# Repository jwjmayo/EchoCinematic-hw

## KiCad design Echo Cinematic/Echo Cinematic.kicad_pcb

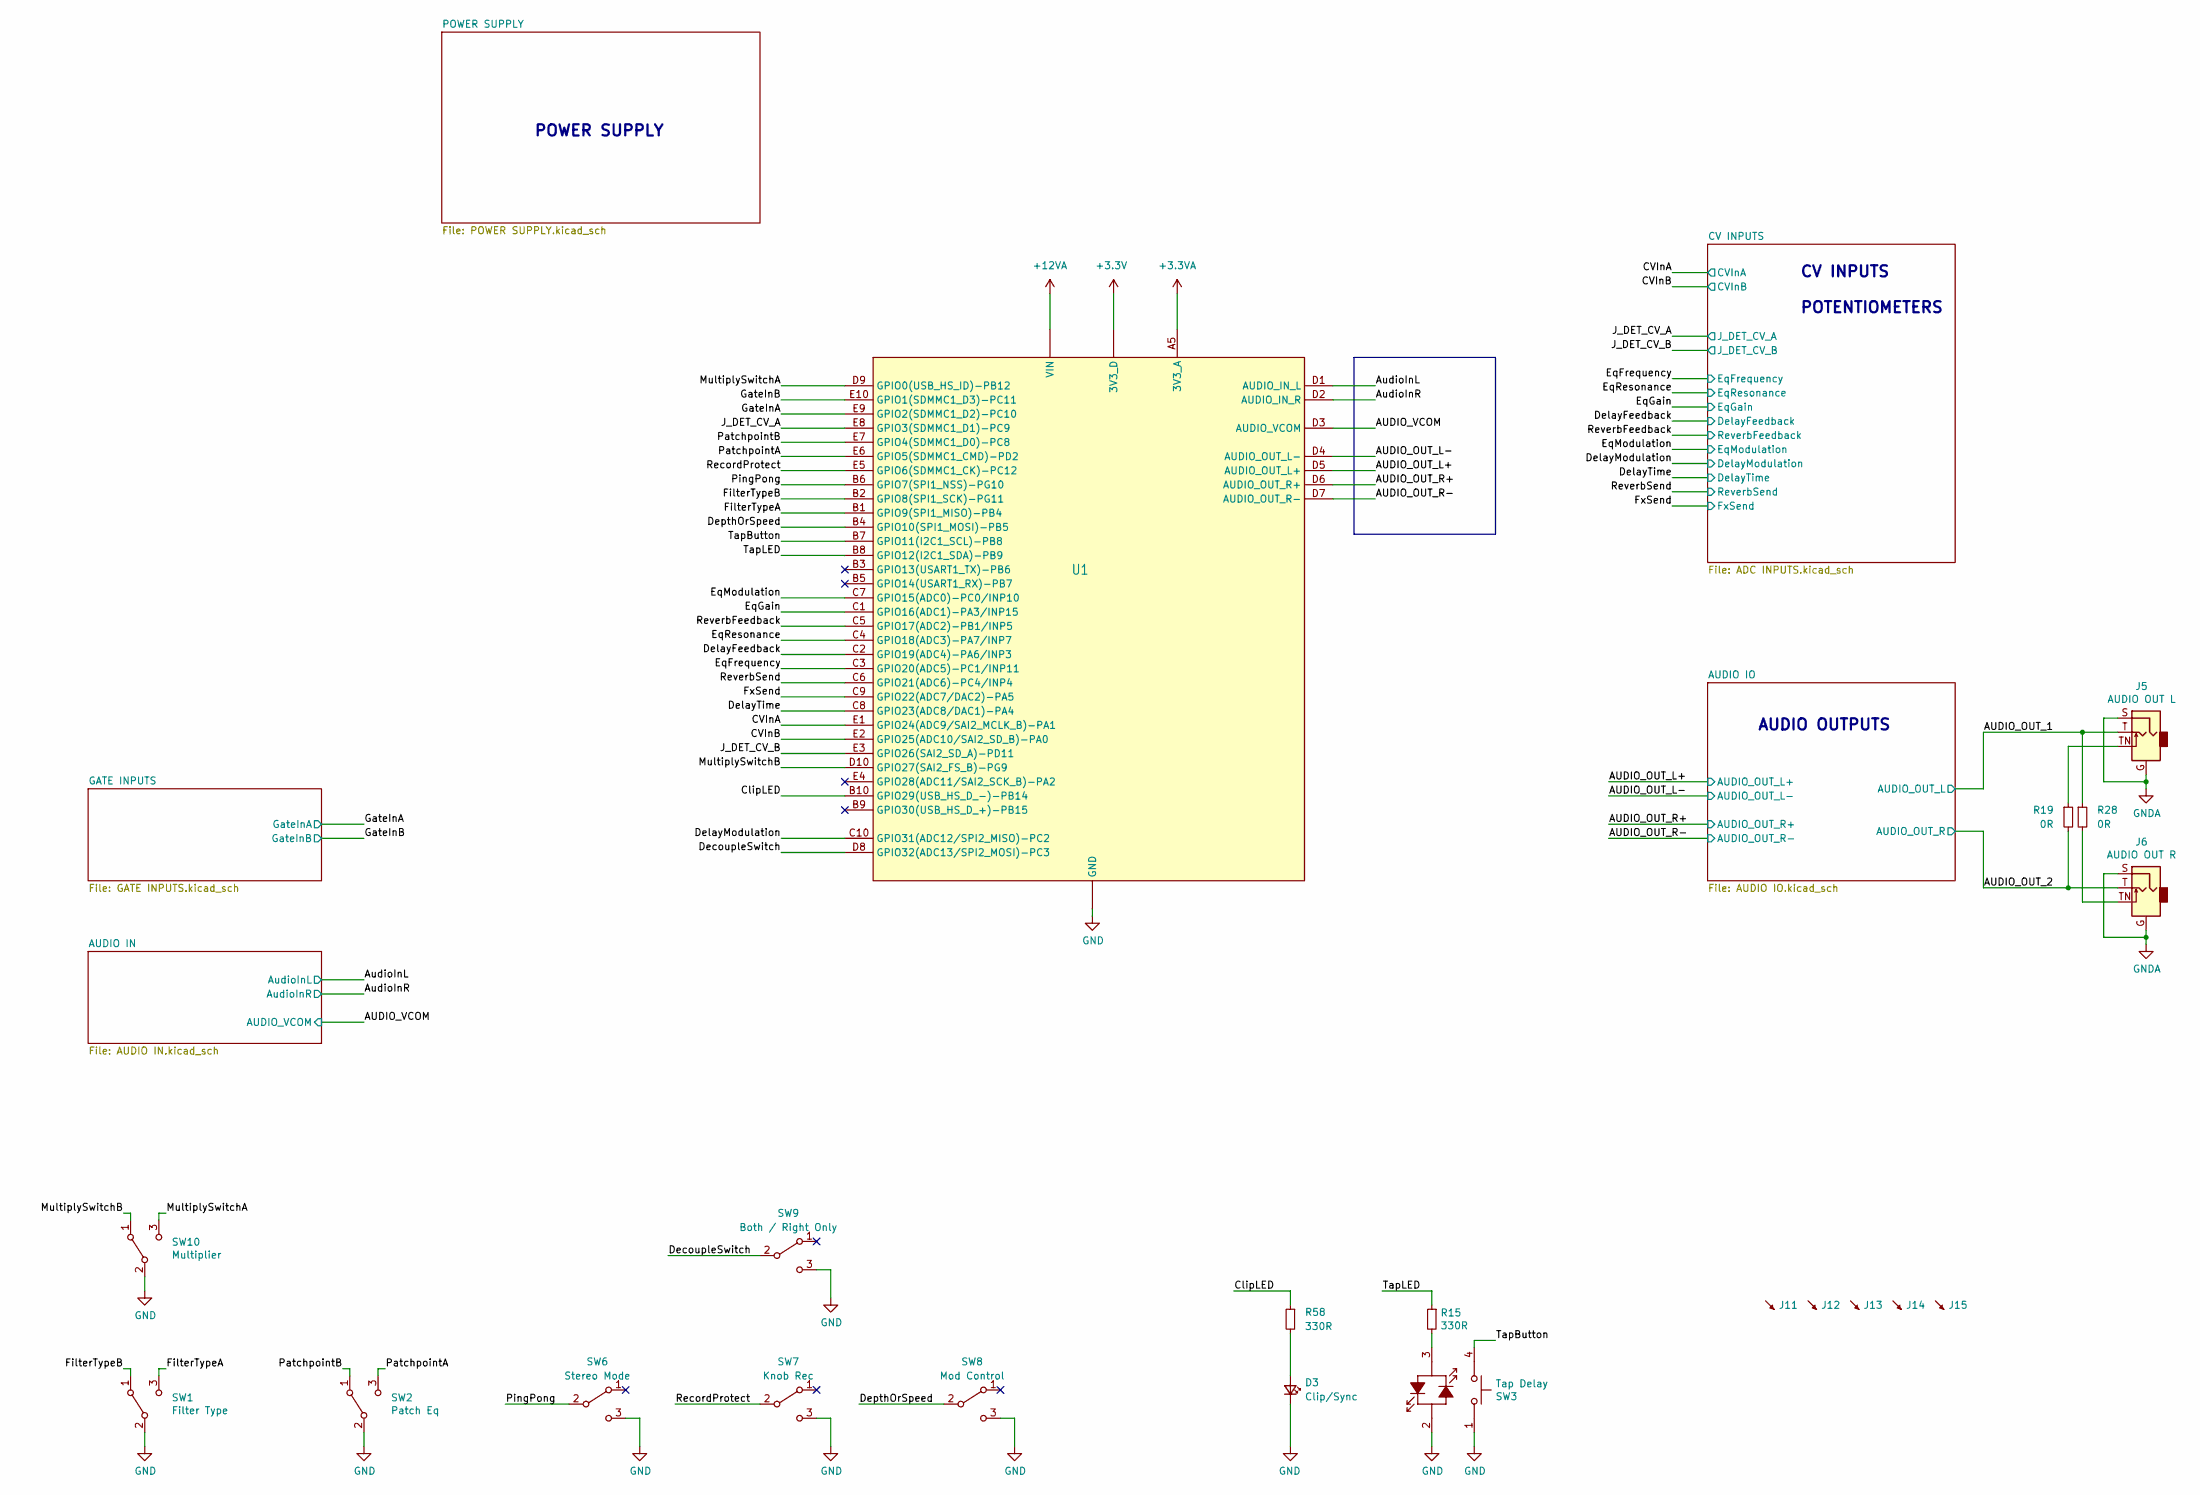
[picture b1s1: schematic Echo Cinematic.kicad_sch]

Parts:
D3: Clip/Sync; LED_D3.0mm
J5: AUDIO OUT L; THONKICONN
J6: AUDIO OUT R; THONKICONN
J11, J12, J13, J14, J15: SYM_Arrow45_Tiny; REF
R15, R58: 330R; R_0603_1608Metric
R19, R28: 0R; R_0603_1608Metric
SW1: Filter Type; SW_DWB1
SW2: Patch Eq; SW_DWB1
SW3: Tap Delay; D6R00F_LED
SW6: Stereo Mode; SW_Slide_1P2T_CK_OS102011MS2Q
SW7: Knob Rec; SW_Slide_1P2T_CK_OS102011MS2Q
SW8: Mod Control; SW_Slide_1P2T_CK_OS102011MS2Q
SW9: Both / Right Only; SW_Slide_1P2T_CK_OS102011MS2Q
SW10: Multiplier; SW_DWB1
U1: ES_DAISY_SEED2_DFM; DAISY_SEED2

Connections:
+3.3V: U1.A3 (3V3_D), U1.A4 (3V3_D); also elsewhere on the board
+3.3VA: U1.A5 (3V3_A); also elsewhere on the board
+12VA: U1.A1 (VIN), U1.A2 (VIN); also elsewhere on the board
/AUDIO_OUT_1: J5.T, R28.1; also elsewhere on the board
/AUDIO_OUT_2: J6.T, R19.2; also elsewhere on the board
/AUDIO_OUT_L+: U1.D5 (AUDIO_OUT_L+); also elsewhere on the board
/AUDIO_OUT_L-: U1.D4 (AUDIO_OUT_L-); also elsewhere on the board
/AUDIO_OUT_R+: U1.D6 (AUDIO_OUT_R+); also elsewhere on the board
/AUDIO_OUT_R-: U1.D7 (AUDIO_OUT_R-); also elsewhere on the board
/AUDIO_VCOM: U1.D3 (AUDIO_VCOM); also elsewhere on the board
/AudioInL: U1.D1 (AUDIO_IN_L); also elsewhere on the board
/AudioInR: U1.D2 (AUDIO_IN_R); also elsewhere on the board
/CVInA: U1.E1 (GPIO24(ADC9/SAI2_MCLK_B)-PA1); also elsewhere on the board
/CVInB: U1.E2 (GPIO25(ADC10/SAI2_SD_B)-PA0); also elsewhere on the board
/ClipLED: R58.1, U1.B10 (GPIO29(USB_HS_D_-)-PB14)
/DecoupleSwitch: SW9.2 (B), U1.D8 (GPIO32(ADC13/SPI2_MOSI)-PC3)
/DelayFeedback: U1.C2 (GPIO19(ADC4)-PA6/INP3); also elsewhere on the board
/DelayModulation: U1.C10 (GPIO31(ADC12/SPI2_MISO)-PC2); also elsewhere on the board
/DelayTime: U1.C8 (GPIO23(ADC8/DAC1)-PA4); also elsewhere on the board
/DepthOrSpeed: SW8.2 (B), U1.B4 (GPIO10(SPI1_MOSI)-PB5)
/EqFrequency: U1.C3 (GPIO20(ADC5)-PC1/INP11); also elsewhere on the board
/EqGain: U1.C1 (GPIO16(ADC1)-PA3/INP15); also elsewhere on the board
/EqModulation: U1.C7 (GPIO15(ADC0)-PC0/INP10); also elsewhere on the board
/EqResonance: U1.C4 (GPIO18(ADC3)-PA7/INP7); also elsewhere on the board
/FilterTypeA: SW1.3 (C), U1.B1 (GPIO9(SPI1_MISO)-PB4)
/FilterTypeB: SW1.1 (A), U1.B2 (GPIO8(SPI1_SCK)-PG11)
/FxSend: U1.C9 (GPIO22(ADC7/DAC2)-PA5); also elsewhere on the board
/GateInA: U1.E9 (GPIO2(SDMMC1_D2)-PC10); also elsewhere on the board
/GateInB: U1.E10 (GPIO1(SDMMC1_D3)-PC11); also elsewhere on the board
/J_DET_CV_A: U1.E8 (GPIO3(SDMMC1_D1)-PC9); also elsewhere on the board
/J_DET_CV_B: U1.E3 (GPIO26(SAI2_SD_A)-PD11); also elsewhere on the board
/MultiplySwitchA: SW10.3 (C), U1.D9 (GPIO0(USB_HS_ID)-PB12)
/MultiplySwitchB: SW10.1 (A), U1.D10 (GPIO27(SAI2_FS_B)-PG9)
/PatchpointA: SW2.3 (C), U1.E6 (GPIO5(SDMMC1_CMD)-PD2)
/PatchpointB: SW2.1 (A), U1.E7 (GPIO4(SDMMC1_D0)-PC8)
/PingPong: SW6.2 (B), U1.B6 (GPIO7(SPI1_NSS)-PG10)
/RecordProtect: SW7.2 (B), U1.E5 (GPIO6(SDMMC1_CK)-PC12)
/ReverbFeedback: U1.C5 (GPIO17(ADC2)-PB1/INP5); also elsewhere on the board
/ReverbSend: U1.C6 (GPIO21(ADC6)-PC4/INP4); also elsewhere on the board
/TapButton: SW3.4 (A), U1.B7 (GPIO11(I2C1_SCL)-PB8)
/TapLED: R15.1, U1.B8 (GPIO12(I2C1_SDA)-PB9)
GND: D3.1 (K), SW1.2 (B), SW2.2 (B), SW3.1, SW3.2, SW6.3 (C), SW7.3 (C), SW8.3 (C), SW9.3 (C), SW10.2 (B), U1.A6 (GND), U1.A7 (GND), U1.A8 (GND), U1.A9 (GND), U1.A10 (GND); also elsewhere on the board
GNDA: J5.G, J5.S, J6.G, J6.S; also elsewhere on the board
unnamed: D3.2 (A), R58.2
unnamed: J5.TN, R19.1
unnamed: J6.TN, R28.2
unnamed: R15.2, SW3.3 (K)

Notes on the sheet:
POWER SUPPLY
CV INPUTS POTENTIOMETERS
AUDIO OUTPUTS

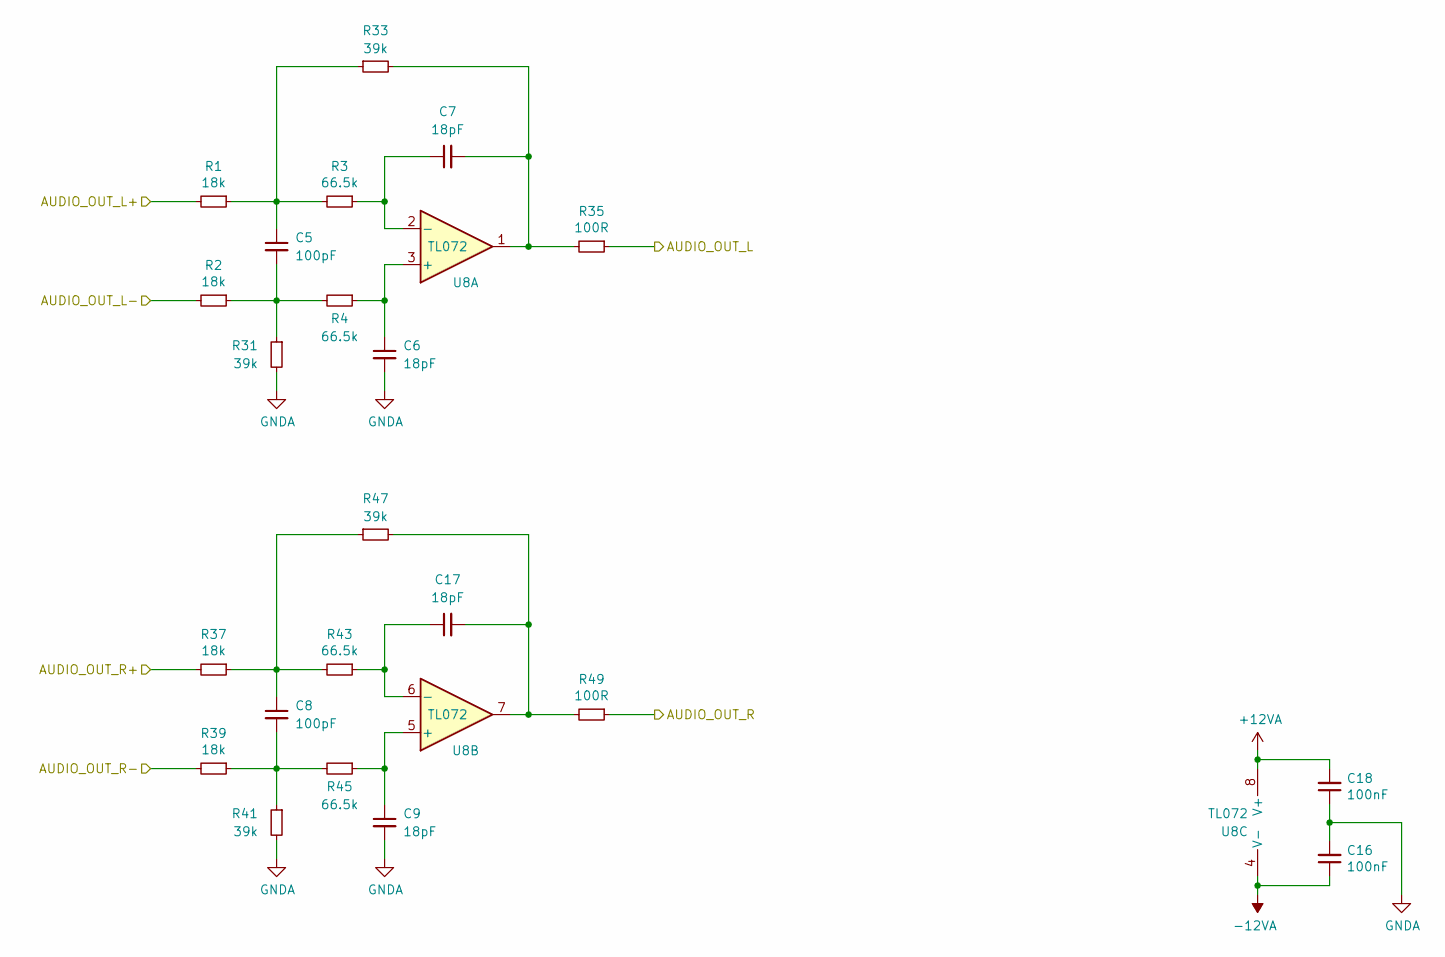
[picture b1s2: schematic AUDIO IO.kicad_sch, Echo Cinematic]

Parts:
C5, C8: 100pF; C_0603_1608Metric
C6, C7, C9, C17: 18pF; C_0603_1608Metric
C16, C18: 100nF; C_0603_1608Metric
R1, R2, R37, R39: 18k; R_0603_1608Metric
R3, R4, R43, R45: 66.5k; R_0603_1608Metric
R31, R33, R41, R47: 39k; R_0603_1608Metric
R35, R49: 100R; R_0603_1608Metric
U8: TL072; SO-8_3.9x4.9mm_P1.27mm

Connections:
+12VA: C18.2, U8.8 (V+); also elsewhere on the board
-12VA: C16.1, U8.4 (V-); also elsewhere on the board
/AUDIO_OUT_1: R35.1; also elsewhere on the board
/AUDIO_OUT_2: R49.1; also elsewhere on the board
/AUDIO_OUT_L+: R1.2; also elsewhere on the board
/AUDIO_OUT_L-: R2.2; also elsewhere on the board
/AUDIO_OUT_R+: R37.2; also elsewhere on the board
/AUDIO_OUT_R-: R39.2; also elsewhere on the board
GNDA: C6.2, C9.2, C16.2, C18.1, R31.2, R41.2; also elsewhere on the board
unnamed: C5.1, R1.1, R3.2, R33.1
unnamed: C5.2, R2.1, R4.2, R31.1
unnamed: C7.2, R33.2, R35.2, U8.1
unnamed: C8.1, R37.1, R43.2, R47.1
unnamed: C8.2, R39.1, R41.1, R45.2
unnamed: C17.2, R47.2, R49.2, U8.7
unnamed: C6.1, R4.1, U8.3 (+)
unnamed: C7.1, R3.1, U8.2 (-)
unnamed: C9.1, R45.1, U8.5 (+)
unnamed: C17.1, R43.1, U8.6 (-)

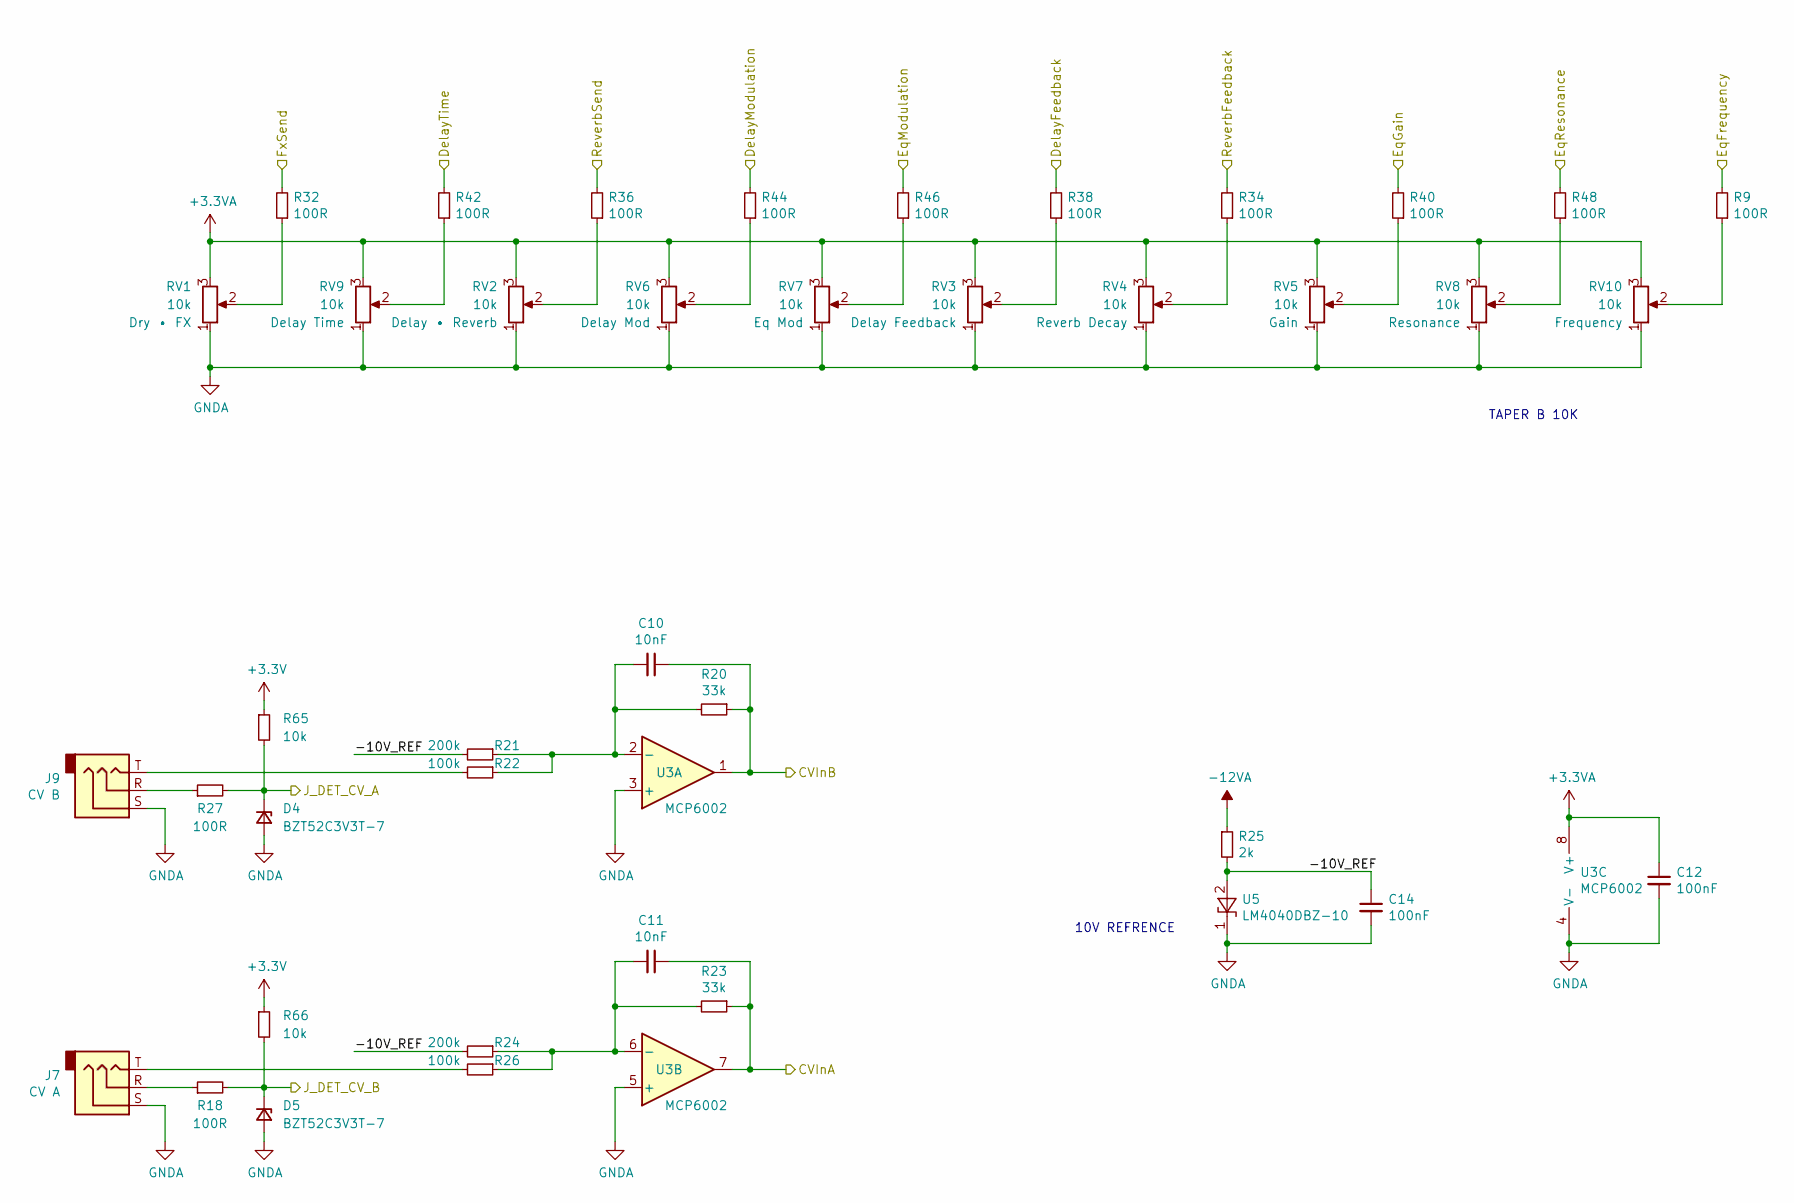
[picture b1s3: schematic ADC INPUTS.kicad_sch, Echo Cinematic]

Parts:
C10, C11: 10nF; C_0603_1608Metric
C12, C14: 100nF; C_0603_1608Metric
D4, D5: BZT52C3V3T-7; D_SOD-523
J7: CV A; THONKICONN_ST
J9: CV B; THONKICONN_ST
R9, R18, R27, R32, R34, R36, R38, R40, R42, R44, R46, R48: 100R; R_0603_1608Metric
R20, R23: 33k; R_0603_1608Metric
R21, R24: 200k; R_0603_1608Metric
R22, R26: 100k; R_0603_1608Metric
R25: 2k; R_0603_1608Metric
R65, R66: 10k; R_0603_1608Metric
RV1, RV2, RV4, RV5, RV6, RV7, RV8: 10k; R0904N
RV3, RV9, RV10: 10k; POT_ALPS
U3: MCP6002; SOIC-8_3.9x4.9mm_P1.27mm
U5: LM4040DBZ-10; SOT-23

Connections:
+3.3V: R65.1, R66.1; also elsewhere on the board
+3.3VA: C12.1, RV1.3, RV2.3, RV3.3, RV4.3, RV5.3, RV6.3, RV7.3, RV8.3, RV9.3, RV10.3, U3.8 (V+); also elsewhere on the board
-12VA: R25.1; also elsewhere on the board
/CV INPUTS/-10V_REF: C14.1, R21.2, R24.2, R25.2, U5.2 (A)
/CVInA: C11.1, R23.1, U3.7; also elsewhere on the board
/CVInB: C10.1, R20.1, U3.1; also elsewhere on the board
/DelayFeedback: R38.2; also elsewhere on the board
/DelayModulation: R44.2; also elsewhere on the board
/DelayTime: R42.2; also elsewhere on the board
/EqFrequency: R9.2; also elsewhere on the board
/EqGain: R40.2; also elsewhere on the board
/EqModulation: R46.2; also elsewhere on the board
/EqResonance: R48.2; also elsewhere on the board
/FxSend: R32.2; also elsewhere on the board
/J_DET_CV_A: D4.1 (K), R27.2, R65.2; also elsewhere on the board
/J_DET_CV_B: D5.1 (K), R18.2, R66.2; also elsewhere on the board
/ReverbFeedback: R34.2; also elsewhere on the board
/ReverbSend: R36.2; also elsewhere on the board
GNDA: C12.2, C14.2, D4.2 (A), D5.2 (A), J7.S, J9.S, RV1.1, RV2.1, RV3.1, RV4.1, RV5.1, RV6.1, RV7.1, RV8.1, RV9.1, RV10.1, U3.3 (+), U3.4 (V-), U3.5 (+), U5.1 (K); also elsewhere on the board
unnamed: J7.R, R18.1
unnamed: J7.T, R26.2
unnamed: J9.R, R27.1
unnamed: J9.T, R22.2
unnamed: R9.1, RV10.2
unnamed: R32.1, RV1.2
unnamed: R34.1, RV4.2
unnamed: R36.1, RV2.2
unnamed: R38.1, RV3.2
unnamed: R40.1, RV5.2
unnamed: R42.1, RV9.2
unnamed: R44.1, RV6.2
unnamed: R46.1, RV7.2
unnamed: R48.1, RV8.2
unnamed: C10.2, R20.2, R21.1, R22.1, U3.2 (-)
unnamed: C11.2, R23.2, R24.1, R26.1, U3.6 (-)

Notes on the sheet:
10V REFRENCE
TAPER B 10K

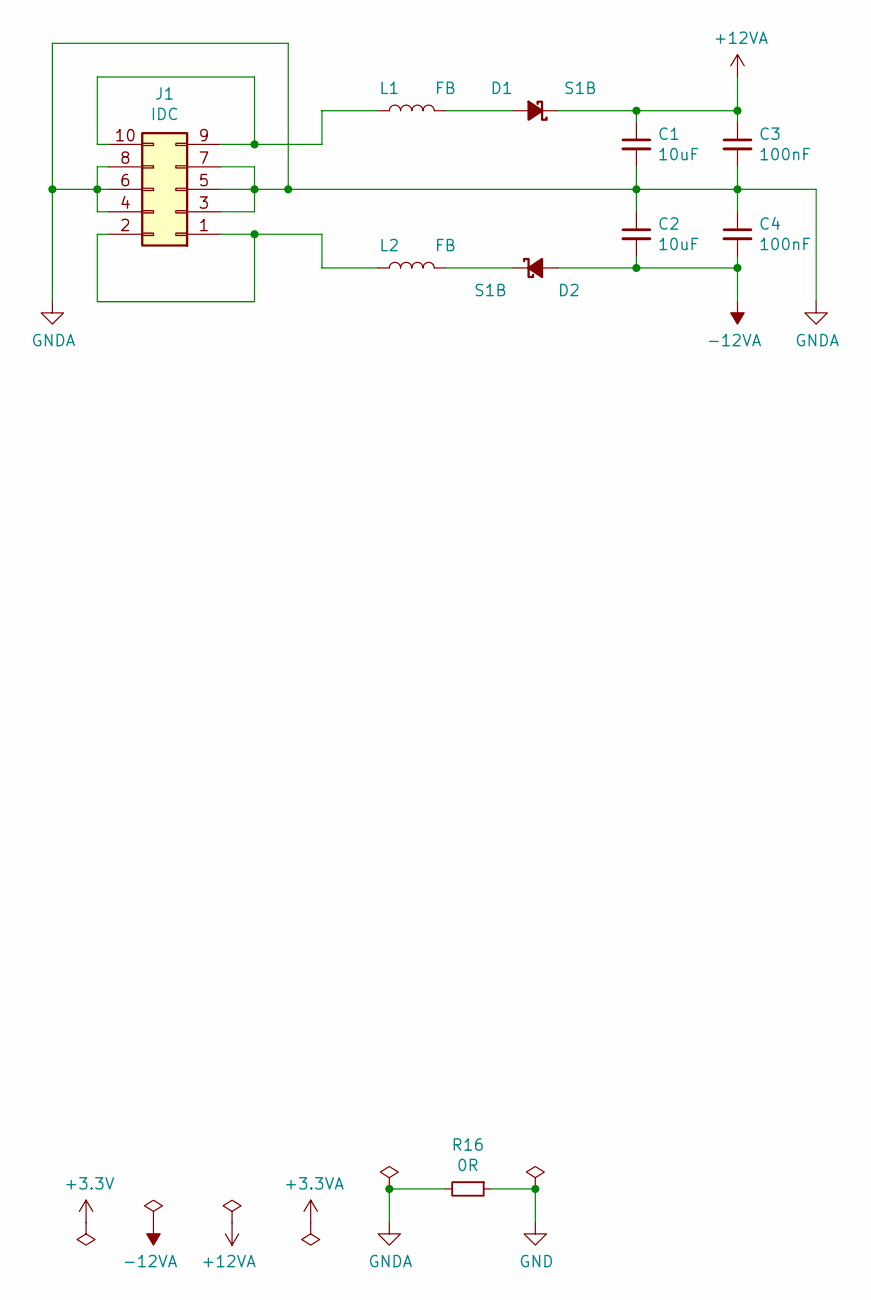
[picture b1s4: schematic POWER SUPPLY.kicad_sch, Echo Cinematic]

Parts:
C1, C2: 10uF; C_0805_2012Metric
C3, C4: 100nF; C_0603_1608Metric
D1, D2: S1B; D_SOD-123
J1: IDC; IDC-Header_2x05_P2.54mm_Vertical
L1, L2: FB; R_0805_2012Metric
R16: 0R; R_0805_2012Metric

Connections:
+12VA: C1.1, C3.1, D1.1 (K); also elsewhere on the board
-12VA: C2.2, C4.2, D2.2 (A); also elsewhere on the board
GND: R16.1; also elsewhere on the board
GNDA: C1.2, C2.1, C3.2, C4.1, J1.3, J1.4, J1.5, J1.6, J1.7, J1.8, R16.2; also elsewhere on the board
unnamed: D1.2 (A), L1.2
unnamed: D2.1 (K), L2.2
unnamed: J1.1, J1.2, L2.1
unnamed: J1.9, J1.10, L1.1

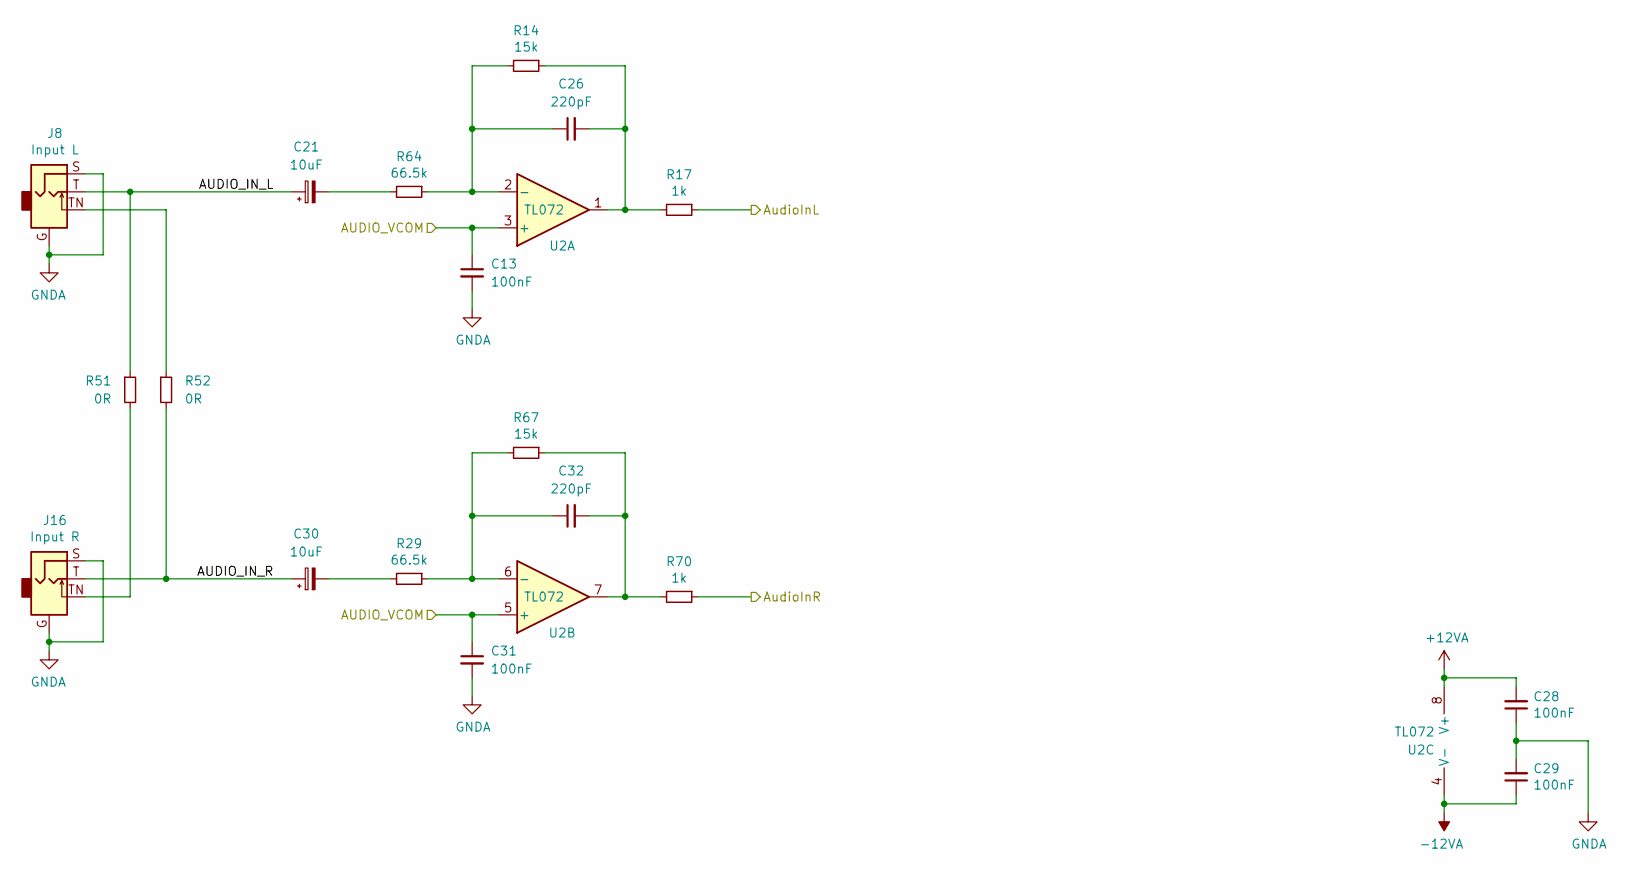
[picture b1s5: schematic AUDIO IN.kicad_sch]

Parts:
C13, C28, C29, C31: 100nF; C_0603_1608Metric
C21, C30: 10uF; CP_EIA-3216-10_Kemet-I
C26, C32: 220pF; C_0603_1608Metric
J8: Input L; THONKICONN
J16: Input R; THONKICONN
R14, R67: 15k; R_0603_1608Metric
R17, R70: 1k; R_0603_1608Metric
R29, R64: 66.5k; R_0603_1608Metric
R51, R52: 0R; R_0603_1608Metric
U2: TL072; SO-8_3.9x4.9mm_P1.27mm

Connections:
+12VA: C28.2, U2.8 (V+); also elsewhere on the board
-12VA: C29.1, U2.4 (V-); also elsewhere on the board
/AUDIO IN/AUDIO_IN_L: C21.1, J8.T, R51.1
/AUDIO IN/AUDIO_IN_R: C30.1, J16.T, R52.2
/AUDIO_VCOM: C13.1, C31.1, U2.3 (+), U2.5 (+); also elsewhere on the board
/AudioInL: R17.1; also elsewhere on the board
/AudioInR: R70.1; also elsewhere on the board
GNDA: C13.2, C28.1, C29.2, C31.2, J8.G, J8.S, J16.G, J16.S; also elsewhere on the board
unnamed: C21.2, R64.2
unnamed: C26.2, R14.1, R17.2, U2.1
unnamed: C30.2, R29.2
unnamed: C32.2, R67.1, R70.2, U2.7
unnamed: J8.TN, R52.1
unnamed: J16.TN, R51.2
unnamed: C26.1, R14.2, R64.1, U2.2 (-)
unnamed: C32.1, R29.1, R67.2, U2.6 (-)

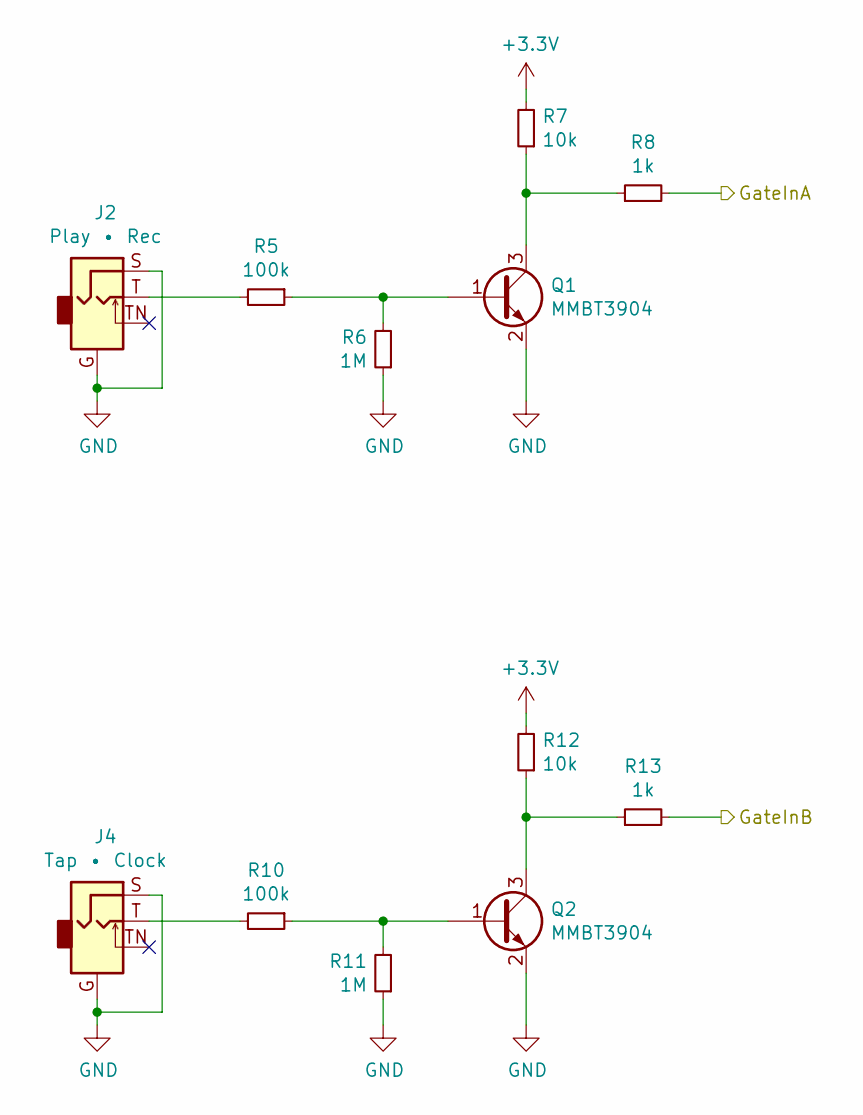
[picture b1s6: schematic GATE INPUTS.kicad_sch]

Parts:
J2: Play • Rec; THONKICONN
J4: Tap • Clock; THONKICONN
Q1, Q2: MMBT3904; SOT-23
R5, R10: 100k; R_0603_1608Metric
R6, R11: 1M; R_0603_1608Metric
R7, R12: 10k; R_0603_1608Metric
R8, R13: 1k; R_0603_1608Metric

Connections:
+3.3V: R7.2, R12.2; also elsewhere on the board
/GateInA: R8.2; also elsewhere on the board
/GateInB: R13.2; also elsewhere on the board
GND: J2.G, J2.S, J4.G, J4.S, Q1.2 (E), Q2.2 (E), R6.1, R11.1; also elsewhere on the board
unnamed: J2.T, R5.2
unnamed: J4.T, R10.2
unnamed: Q1.1 (B), R5.1, R6.2
unnamed: Q1.3 (C), R7.1, R8.1
unnamed: Q2.1 (B), R10.1, R11.2
unnamed: Q2.3 (C), R12.1, R13.1

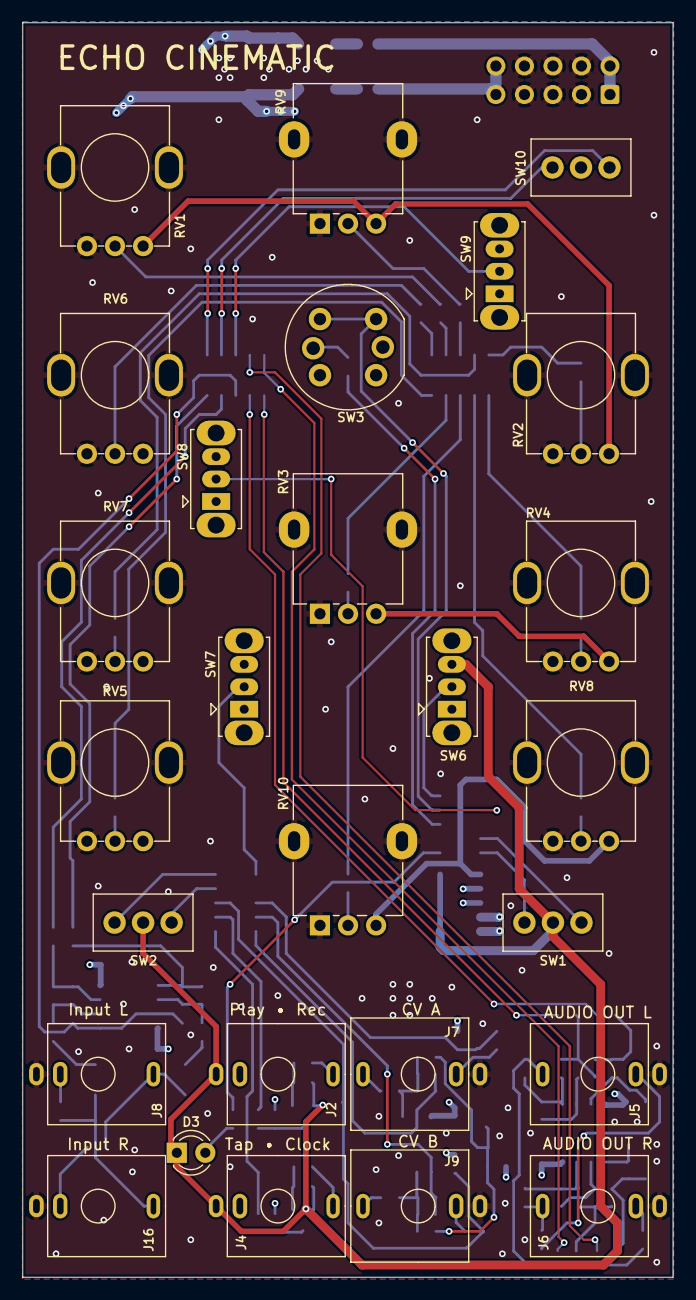
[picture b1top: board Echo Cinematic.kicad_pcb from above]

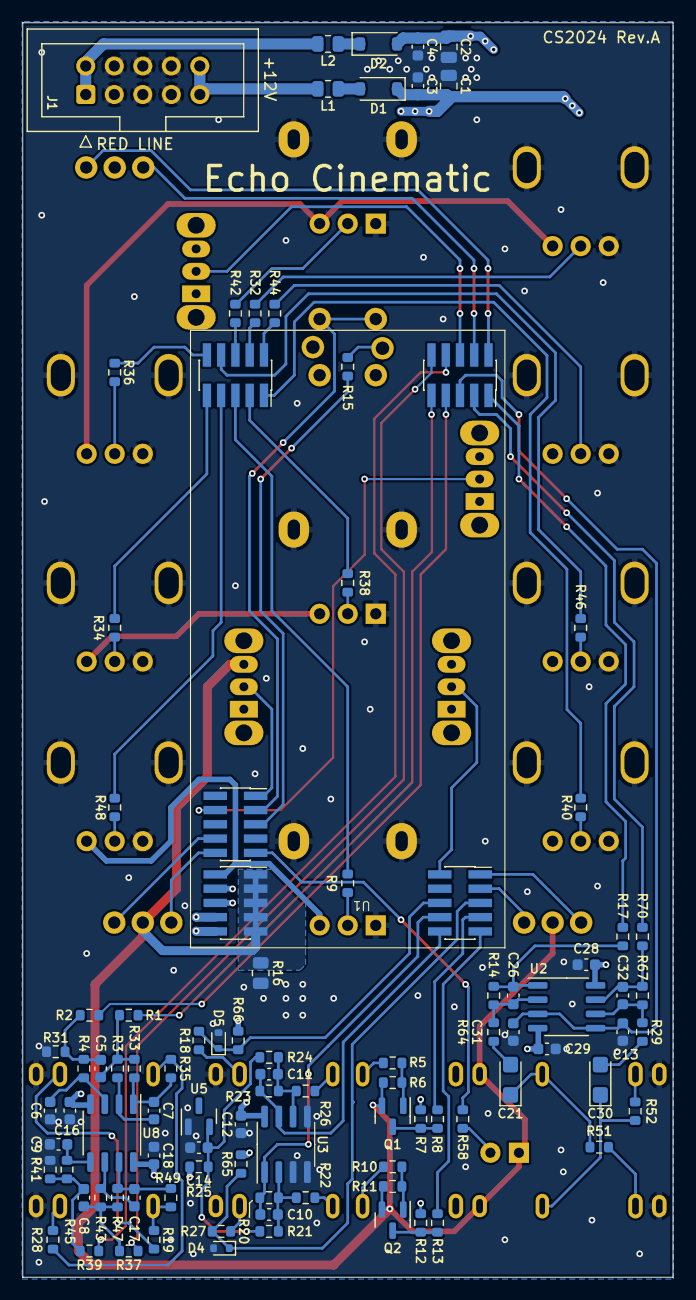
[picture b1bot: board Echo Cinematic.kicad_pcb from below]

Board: 4 copper layers, 57.9 x 111.7 mm, 126 parts (99 on the bottom side), 95 nets.

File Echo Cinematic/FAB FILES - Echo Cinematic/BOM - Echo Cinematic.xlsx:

Designator | QTY | Comment | Footprint | LCSC Part # | MPN
C1, C2 | 2 | 10uF | 805 | C15850
C3, C4, C12, C13, C14, C16, C18, C28, C29, C31 | 10 | 100nF | 603 | C14663
C5, C8 | 2 | 100pF | 603 | C14858
C6, C7, C9, C17 | 4 | 18pF | 603 | C1647
C10, C11 | 2 | 10nF | 603 | C57112
C21, C30 | 2 | 10uF | CASE-A-3216 | C7171
C26, C32 | 2 | 220pF | 603 | C1603
D1, D2 | 2 | PMEG2010ER,115 | SOD-123W | C82288
D3 | 1 | Clip/Sync | FOOTPRINTS:LED_D3.0mm | DNP
D4, D5 | 2 | BZT52C3V3T-7 | SOD-523 | C151563
J1 | 1 | IDC | Plugin,P=2.54mm | C5665
J2 | 1 | Play Rec | FOOTPRINTS:THONKICONN | DNP
J4 | 1 | Tap Clock | FOOTPRINTS:THONKICONN | DNP
J5 | 1 | AUDIO OUT L | FOOTPRINTS:THONKICONN | DNP
J6 | 1 | AUDIO OUT R | FOOTPRINTS:THONKICONN | DNP
J7 | 1 | CV A | FOOTPRINTS:THONKICONN_ST | DNP
J8 | 1 | Input L | FOOTPRINTS:THONKICONN | DNP
J9 | 1 | CV B | FOOTPRINTS:THONKICONN_ST | DNP
J11, J12, J13, J14, J15 | 5 | 1.27mm Female | SMD,P=1.27mm | C3975131
J16 | 1 | Input R | FOOTPRINTS:THONKICONN | DNP
L1, L2 | 2 | FB | 805 | C1017
Q1, Q2 | 2 | MMBT3904 | Package_TO_SOT_SMD:SOT-23 | C20526
R1, R2, R37, R39 | 4 | 18k | 603 | C25810
R3, R4, R29, R43, R45, R64 | 6 | 66.5k | 603 | C423022
R5, R10, R22, R26 | 4 | 100k | 603 | C25803
R6, R11 | 2 | 1M | 603 | C22935
R7, R12, R65, R66 | 4 | 10k | 603 | C25804
R8, R13, R17, R70 | 4 | 1k | 603 | C21190
R9, R18, R27, R32, R34, R35, R36, R38, R40, R42, R44, R46, R48, R49 | 14 | 100R | 603 | C22775
R14, R67 | 2 | 15k | 603 | C22809
R15, R58 | 2 | 330R | 603 | C23138
R16 | 1 | 0R | 805 | C17477
R19, R28, R51, R52 | 4 | 0R | 603 | C21189
R20, R23 | 2 | 33k | 603 | C4216
R21, R24 | 2 | 200k | 603 | C25811
R25 | 1 | 2k | 603 | C22975
R31, R33, R41, R47 | 4 | 39k | 603 | C23153
RV1, RV2, RV4, RV5, RV6, RV7, RV8 | 7 | 10k | FOOTPRINTS:R0904N | DNP
RV3, RV9, RV10 | 3 | 10k | FOOTPRINTS:POT_ALPS | DNP
SW1 | 1 | Filter Type | FOOTPRINTS:SW_DWB1 | DNP
SW2 | 1 | Patch Eq | FOOTPRINTS:SW_DWB1 | DNP
SW3 | 1 | Tap Delay | FOOTPRINTS:D6R00F_LED | DNP
SW6 | 1 | Stereo Mode | FOOTPRINTS:SW_Slide_1P2T_CK_OS102011MS2Q | DNP
SW7 | 1 | Knob Rec | FOOTPRINTS:SW_Slide_1P2T_CK_OS102011MS2Q | DNP
SW8 | 1 | Mod Control | FOOTPRINTS:SW_Slide_1P2T_CK_OS102011MS2Q | DNP
SW9 | 1 | Both / Right Only | FOOTPRINTS:SW_Slide_1P2T_CK_OS102011MS2Q | DNP
SW10 | 1 | Multiplier | FOOTPRINTS:SW_DWB1 | DNP
U2, U8 | 2 | TL072 | SOIC-8 | C6961
U3 | 1 | MCP6002 | SOIC-8 | C7377
U5 | 1 | LM4040DBZ-10 | Package_TO_SOT_SMD:SOT-23 | C201738

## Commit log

2024-03-25 Initial commit, project files added
2024-03-25 Added input jack switching circuits, fab files updated and finalized.
